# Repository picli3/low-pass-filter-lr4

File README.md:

# low-pass-filter-lr4

Filtro pasa bajos activo Linkwitz-Riley de cuarto orden, pensado para subwoofer o cruces activos en sistemas de audio.

## Qué incluye
- esquemáticos o archivos de diseño en KiCad
- PCB o documentación asociada
- base reutilizable para análisis, fabricación o mejora del proyecto

## Propósito general
Este repositorio busca concentrar el diseño de hardware del proyecto en un formato editable y reutilizable, facilitando pruebas, documentación y futuras iteraciones del circuito.

## Vista del proyecto

### Render 3D del PCB

### Render del módulo ensamblado

### Layout del PCB

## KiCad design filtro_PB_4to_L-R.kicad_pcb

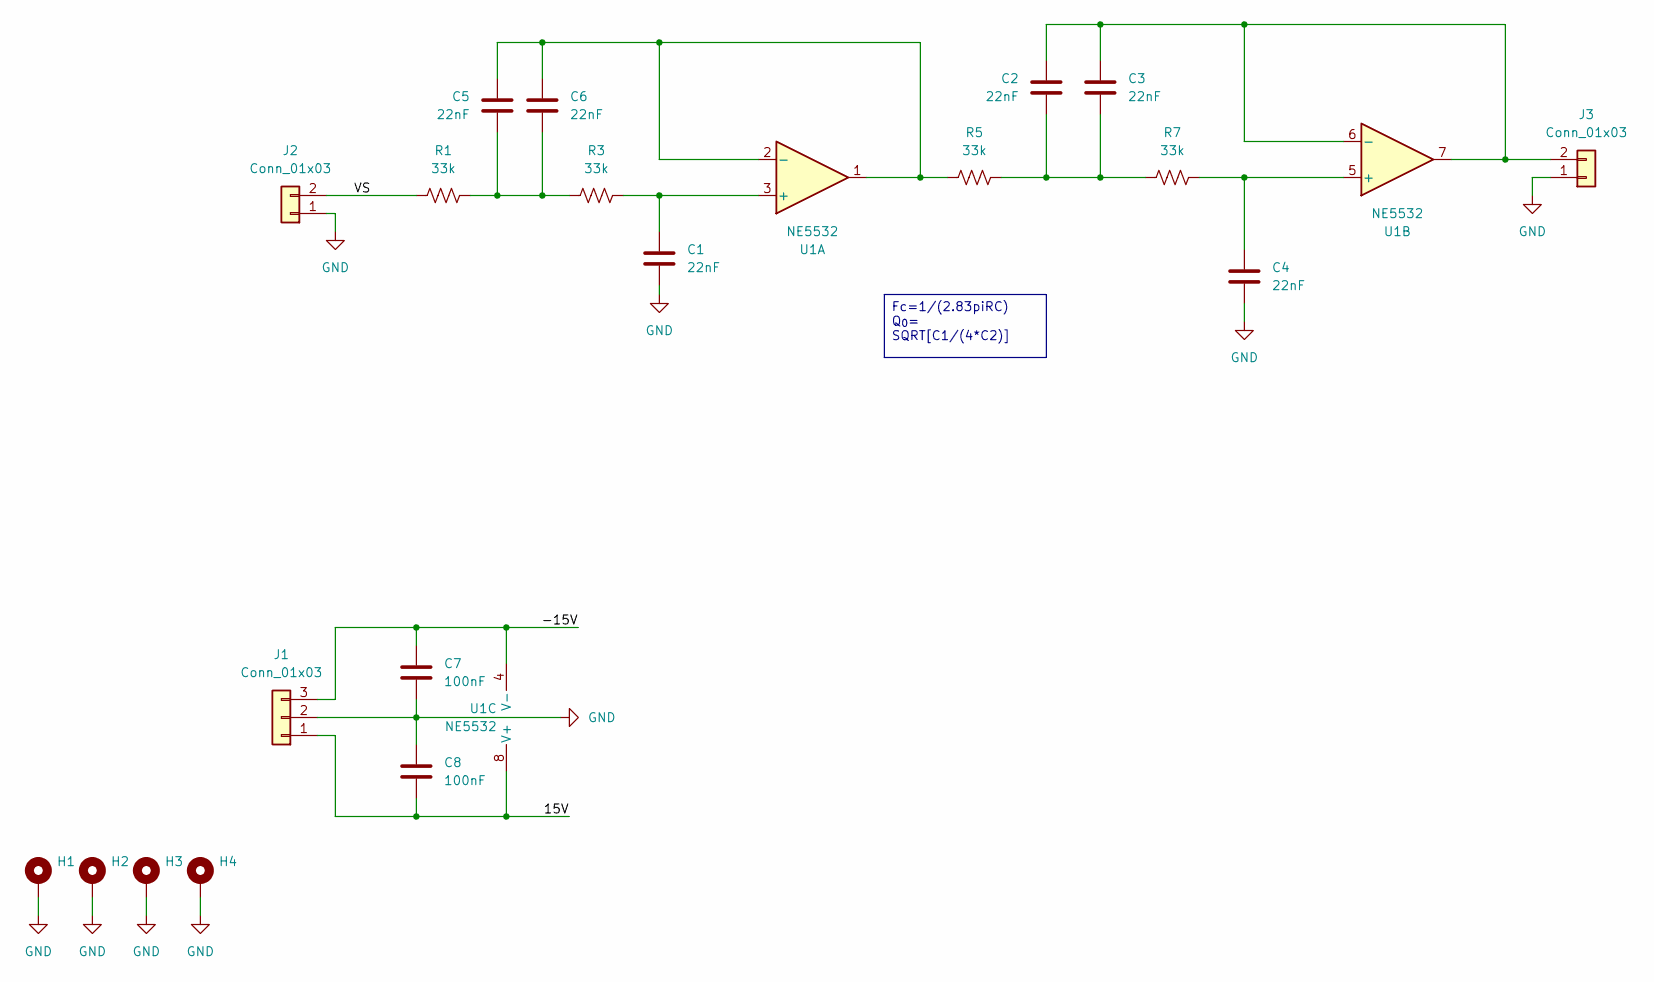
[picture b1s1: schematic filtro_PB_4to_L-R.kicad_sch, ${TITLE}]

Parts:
C1, C2, C3, C4, C5, C6: 22nF; C_Rect_L7.2mm_W2.5mm_P5.00mm_FKS2_FKP2_MKS2_MKP2
C7, C8: 100nF; C_Disc_D5.0mm_W2.5mm_P2.50mm
H1, H2, H3, H4: MountingHole_Pad; MountingHole_3.2mm_M3_DIN965_Pad
J1: Conn_01x03; PinHeader_1x03_P2.54mm_Vertical
J2, J3: Conn_01x03; PinHeader_1x02_P2.54mm_Vertical
R1, R3, R5, R7: 33k; R_Axial_DIN0207_L6.3mm_D2.5mm_P10.16mm_Horizontal
U1: NE5532; DIP-8_W7.62mm_LongPads

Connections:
/15V: C8.1, J1.1, U1.8 (V+)
/-15V: C7.2, J1.3, U1.4 (V-)
/VS: J2.2, R1.2
GND: C1.1, C4.1, C7.1, C8.2, H1.1, H2.1, H3.1, H4.1, J1.2, J2.1, J3.1
unnamed: C2.1, C3.1, R5.1, R7.2
unnamed: C5.1, C6.1, R1.1, R3.2
unnamed: C2.2, C3.2, J3.2, U1.6 (-), U1.7
unnamed: C1.2, R3.1, U1.3 (+)
unnamed: C5.2, C6.2, R5.2, U1.1, U1.2 (-)
unnamed: C4.2, R7.1, U1.5 (+)

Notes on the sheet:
Fc=1/(2.83piRC) Q_{0}= SQRT[C1/(4*C2)]

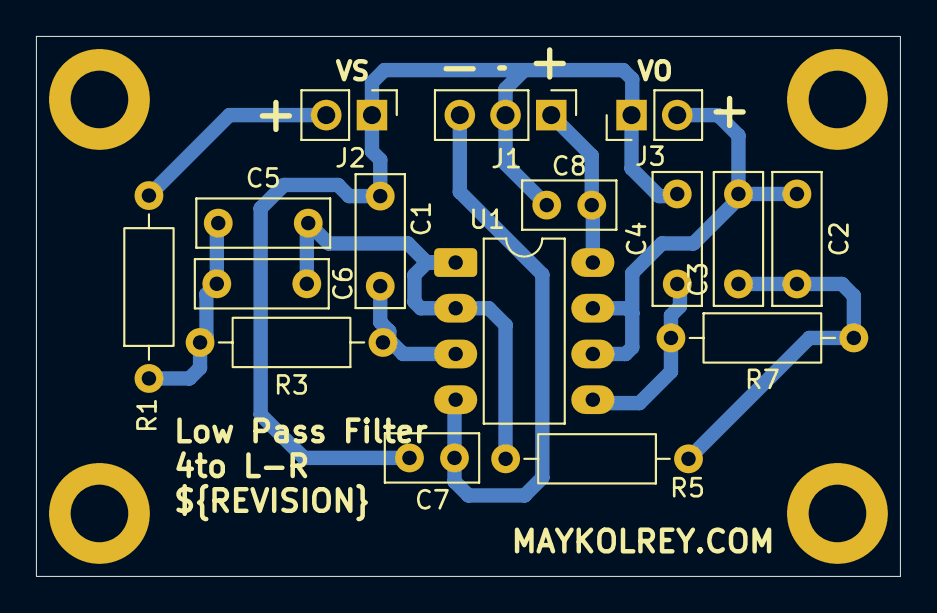
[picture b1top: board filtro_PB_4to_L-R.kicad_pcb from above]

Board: 2 copper layers, 48.0 x 30.0 mm, 20 parts (0 on the bottom side), 10 nets.

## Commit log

2025-11-01 primer commit
2025-11-01 agregando esquematico
2025-11-01 agregando QR de documentacion
2025-11-01 agregando ibom
2026-04-29 Agrega README con descripción inicial del proyecto
2026-04-30 Add project images for issue #2
2026-04-30 docs: add project images to README
2026-04-30 docs: adjust README image layout
2026-04-30 docs: add project BOM to README
2026-04-30 Fix J2 and J3 connector values
2026-04-30 Revert "Add project images for issue #2"
